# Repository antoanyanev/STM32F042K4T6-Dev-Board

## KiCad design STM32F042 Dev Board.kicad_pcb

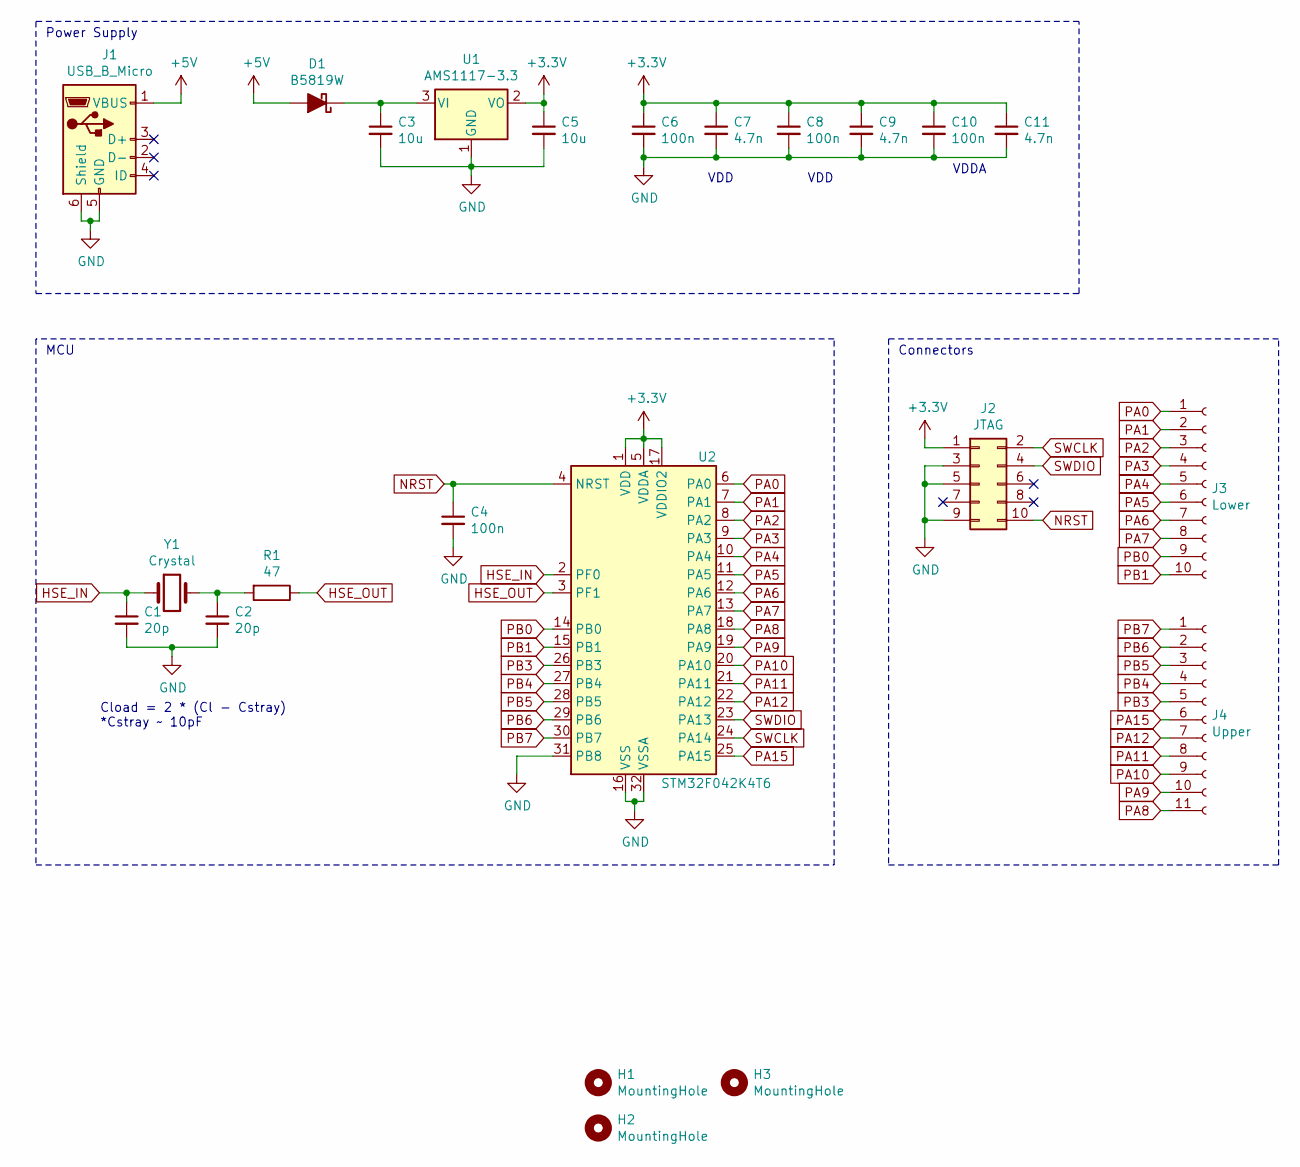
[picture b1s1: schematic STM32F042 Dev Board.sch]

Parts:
C1, C2: 20p; C_0805_2012Metric
C3, C5: 10u; C_0805_2012Metric
C4, C6, C8, C10: 100n; C_0805_2012Metric
C7, C9, C11: 4.7n; C_0805_2012Metric
D1: B5819W; D_SOD-123
H1, H2, H3: MountingHole; MountingHole_2.5mm
J1: USB_B_Micro; USB_Micro-B_Amphenol_10103594-0001LF_Horizontal
J2: JTAG; PinHeader_2x05_P2.54mm_Vertical
J3: Lower; PinHeader_1x10_P2.54mm_Vertical
J4: Upper; PinHeader_1x11_P2.54mm_Vertical
R1: 47; R_0805_2012Metric
U1: AMS1117-3.3; SOT-223-3_TabPin2
U2: STM32F042K4T6; LQFP-32_7x7mm_P0.8mm
Y1: Crystal; Crystal_SMD_HC49-SD

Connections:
+3V3: C5.1, C6.1, C7.1, C8.1, C9.1, C10.1, C11.1, J2.1, U1.2 (VO), U2.1 (VDD), U2.5 (VDDA), U2.17 (VDDIO2)
+5V: D1.2 (A), J1.1 (VBUS)
GND: C1.2, C2.2, C3.2, C4.2, C5.2, C6.2, C7.2, C8.2, C9.2, C10.2, C11.2, J1.5 (GND), J1.6 (Shield), J2.3, J2.5, J2.9, U1.1 (GND), U2.16 (VSS), U2.31 (PB8), U2.32 (VSSA)
HSE_IN: C1.1, U2.2 (PF0), Y1.1
HSE_OUT: R1.1, U2.3 (PF1)
NRST: C4.1, J2.10, U2.4 (NRST)
unnamed: C2.1, R1.2, Y1.2
unnamed: C3.1, D1.1 (K), U1.3 (VI)
PA0: J3.1, U2.6 (PA0)
PA1: J3.2, U2.7 (PA1)
PA2: J3.3, U2.8 (PA2)
PA3: J3.4, U2.9 (PA3)
PA4: J3.5, U2.10 (PA4)
PA5: J3.6, U2.11 (PA5)
PA6: J3.7, U2.12 (PA6)
PA7: J3.8, U2.13 (PA7)
PA8: J4.11, U2.18 (PA8)
PA9: J4.10, U2.19 (PA9)
PA10: J4.9, U2.20 (PA10)
PA11: J4.8, U2.21 (PA11)
PA12: J4.7, U2.22 (PA12)
PA15: J4.6, U2.25 (PA15)
PB0: J3.9, U2.14 (PB0)
PB1: J3.10, U2.15 (PB1)
PB3: J4.5, U2.26 (PB3)
PB4: J4.4, U2.27 (PB4)
PB5: J4.3, U2.28 (PB5)
PB6: J4.2, U2.29 (PB6)
PB7: J4.1, U2.30 (PB7)
SWCLK: J2.2, U2.24 (PA14)
SWDIO: J2.4, U2.23 (PA13)

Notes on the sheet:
Cload = 2 * (Cl - Cstray) *Cstray ~~ 10pF
VDDA
VDD
Power Supply
MCU
Connectors

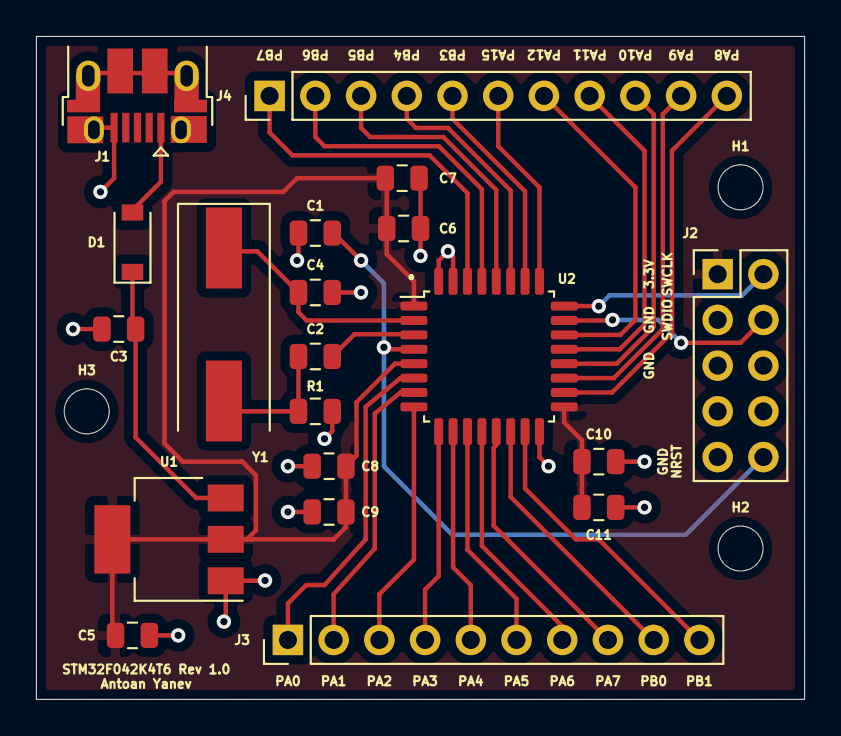
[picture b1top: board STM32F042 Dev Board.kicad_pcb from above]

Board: 2 copper layers, 42.7 x 36.8 mm, 23 parts (0 on the bottom side), 31 nets.

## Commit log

2021-04-02 STM32F042K4T6 Dev Board
